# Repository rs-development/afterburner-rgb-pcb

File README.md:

# Work in Progress

# RGB Led Mount for Voron Afterburner Extruder
Because RGB

# LICENSE
<br />This work is licensed under a <a rel="license" href="http://creativecommons.org/licenses/by-sa/3.0/">Creative Commons Attribution-ShareAlike 3.0 Unported License</a>.

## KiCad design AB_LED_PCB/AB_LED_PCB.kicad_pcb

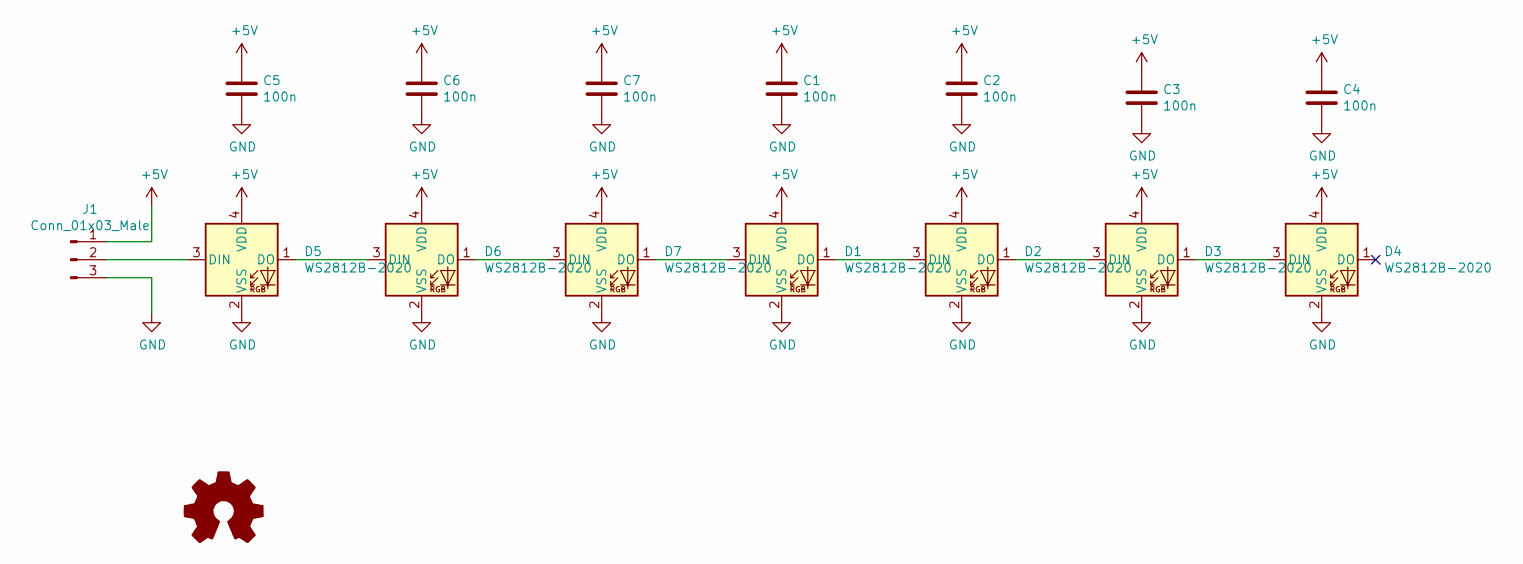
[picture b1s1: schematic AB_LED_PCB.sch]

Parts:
C1, C2, C3, C4, C5, C6, C7: 100n; C_0402_1005Metric
D1, D2, D3, D4, D5, D6, D7: WS2812B-2020; LED_WS2812B-2020_2.2x2.0mm_P1.0mm
J1: Conn_01x03_Male; PinHeader_1x03_P2.54mm_Horizontal
SYM1: Logo_Open_Hardware_Small; OSHW-Logo2_7.3x6mm_SilkScreen

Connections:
+5V: C1.1, C2.1, C3.1, C4.1, C5.1, C6.1, C7.1, D1.4 (VDD), D2.4 (VDD), D3.4 (VDD), D4.4 (VDD), D5.4 (VDD), D6.4 (VDD), D7.4 (VDD), J1.1
GND: C1.2, C2.2, C3.2, C4.2, C5.2, C6.2, C7.2, D1.2 (VSS), D2.2 (VSS), D3.2 (VSS), D4.2 (VSS), D5.2 (VSS), D6.2 (VSS), D7.2 (VSS), J1.3
unnamed: D1.1 (DO), D2.3 (DIN)
unnamed: D1.3 (DIN), D7.1 (DO)
unnamed: D2.1 (DO), D3.3 (DIN)
unnamed: D3.1 (DO), D4.3 (DIN)
unnamed: D5.1 (DO), D6.3 (DIN)
unnamed: D5.3 (DIN), J1.2
unnamed: D6.1 (DO), D7.3 (DIN)

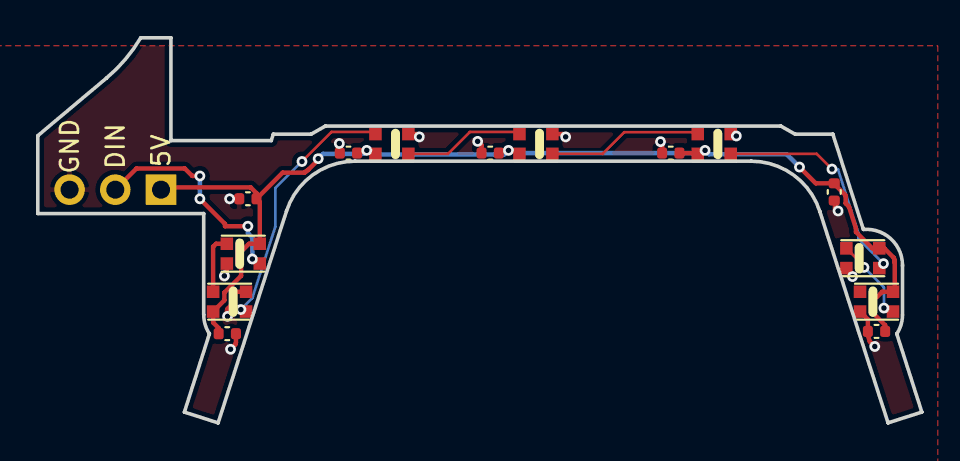
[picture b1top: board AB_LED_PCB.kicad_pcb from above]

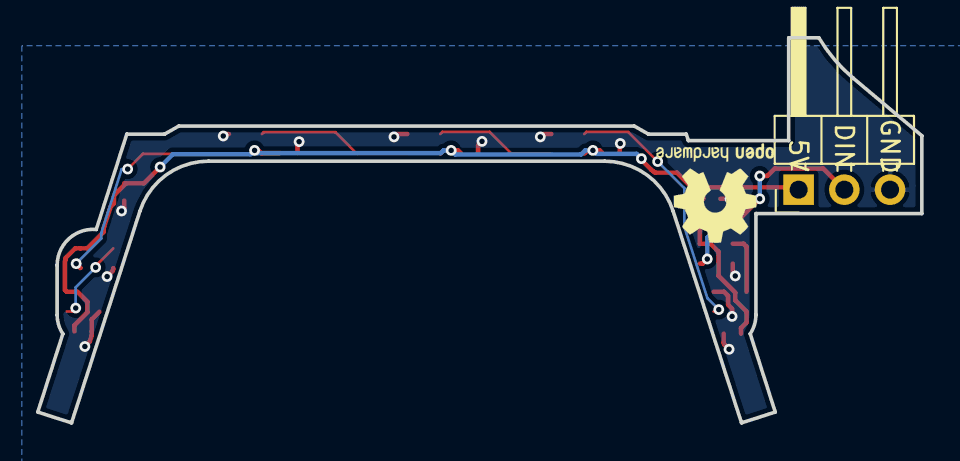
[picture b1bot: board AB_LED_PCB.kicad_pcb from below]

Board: 2 copper layers, 49.1 x 21.4 mm, 16 parts (2 on the bottom side), 9 nets.

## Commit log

2021-04-06 added license and readme
2021-04-06 added logo and routing
2021-04-06 fixed ercs
2021-04-06 added production data
